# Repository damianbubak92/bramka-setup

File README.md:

# Bramka IoT - Setup & Development Repository

Repozytorium konfiguracji i kodu dla bramki IoT na AM62 SoC (SK-AM62B-P1 dev kit).

## Architektura

- **SoC**: TI AM62 (Cortex-A53 quad + Cortex-M4F + Cortex-R5F)
- **Linux**: Arago 2025.01 (kernel 6.18.13-ti, ARM64)
- **Komunikacja**: Linux ↔ M4F przez RPMsg (binary protocol z CRC16)
- **Język aplikacji Linux**: Go 1.23.x (instalowany przez `Gateway/Setup/modules/04-go.sh`)
- **Firmware M4F**: TI MCU+ SDK 12.00, NoRTOS

## Struktura repo

> Ten README opisuje **wczesny stan (sama bramka, RPMsg)**. Projekt urósł do
> **monorepo `SmartHome`** (engine M4F, CC1310 RF, nody, apka Android) — pełny
> aktualny stan, konwencje i Session Log w **`CLAUDE.md`**. (Repo na GitHub wciąż
> nazwany `bramka-setup`; może zostać przemianowany na `SmartHome`.)

```
SmartHome/                (zmigrowane z bramka-setup 2026-06-29)
├── Gateway/              # bramka (A53 Linux + M4F + CC1310 RF)
│   ├── Software/         #   Go: rpmsg-service (RPMsg bridge + HTTP/WS API, cgo)
│   ├── Firmware/         #   CCS: M4F (gateway_m4f) + CC1310 (gateway_cc1310)
│   ├── Setup/            #   setup.sh, modules/, systemd/, tools/, config.sh
│   └── Hardware/         #   carrier board (TODO)
├── Nodes/                # TempHumNode/{Firmware = temphum_node, Hardware}, Light/Solar (szkielety)
├── Apps/                 # MobileApp/AndroidApp/SmartHomeV2 (Android Studio); iOS/, WebApp/ (TODO)
├── Shared/               # Protocol/ (node_protocol.h, protocol.h, spi_frame.h — SINGLE SOURCE), KiCadLib/
└── Docs/
```

## Quick start

### 1. Instalacja bramki (od zera)
```bash
# 1. Świeży flash karty SD (Etcher)
# 2. SSH do bramki:
git clone https://github.com/damianbubak92/bramka-setup
cd bramka-setup/Gateway/Setup
sudo ./setup.sh    # network + tools + m4f firmware backup + GO INSTALL
reboot
# 3. Z laptopa:
Deploy-M4F                                            # custom M4F firmware
Deploy-Go -ServiceName rpmsg-service -Build           # build Go binary
Install-GoService -ServiceName rpmsg-service          # systemd unit
```

### 2. Workflow developerski

**M4F firmware** (z laptopa, PowerShell):
```powershell
# Build w CCS Theia (Ctrl+Shift+B)
Deploy-M4F                         # 5s logów
Deploy-M4F -LogForever             # logi do Ctrl+C
Deploy-M4F -NoLogs                 # bez logów
```
> `m4f-reload` (woła go `Deploy-M4F`) sam zatrzymuje `rpmsg-service` przed
> `echo stop` M4F i restartuje po starcie. Bez tego serwis wykryłby zniknięcie
> `/dev/rpmsg` jako PEER DEAD i zrobił reboot bramki w trakcie podmiany firmware.

**Go service** (z laptopa, PowerShell):
```powershell
Deploy-Go -ServiceName protocol-test -Build -Run
```

### 3. Monitor

```bash
ssh root@bramka-01
m4f-watch                          # live M4F trace
```

## Status (v5)

- ✅ Setup script (Linux configuration, network, tools, M4F firmware)
- ✅ M4F graceful shutdown handler (hot-swap firmware bez reboot)
- ✅ Go runtime (cgo działa, łączy się z shared C header)
- ✅ Binary protocol (CRC16-CCITT, packed wire format, big-endian)
- ✅ HELLO/HELLO_ACK exchange w binary protocol
- ✅ State machine: DISCONNECTED → HELLO_SENT → CONNECTED → DEAD
- ✅ Reliable DATA delivery (ACK + 3 retries z 1s timeout)
- ✅ Idempotency check (duplicate detection w M4F)
- ✅ EVENT (M4F→Linux autonomous events z ACK + retry)
- ✅ Bidirectional reliable messaging w pełni działa (~5ms RTT)
- ✅ **Warstwa A**: systemd watchdog dla Go service (`Restart=on-failure` + `StartLimitBurst=3`)
- ⏸️ **Warstwa B**: M4F self-watchdog (RTI) - skipped, do later
- ⏳ **Warstwa C**: M4F → Linux reset via DMSC
- ✅ **Warstwa D**: Linux HW watchdog (`/dev/watchdog` via systemd, `RuntimeWatchdogSec=30`) - konfigurowany przez `modules/05-watchdog.sh` (był zgubiony przy re-flashu, przywrócony 15.06.2026)
- ✅ **panic_on_oops=1** (`modules/06-kernel-panic.sh`): oops → pełny panic → łapie Warstwa D. Domyka lukę "oops kaleczy kernel ale systemd dalej klepie watchdog → nic nie łapie"
- ✅ **Boot accounting** (`modules/07-boot-accounting.sh`): licznik bootów + atrybucja przyczyny (breadcrumb Go / kernel panic / clean-shutdown / hard reset) + alarm reboot-storm (sparametryzowany `/etc/bramka/boot-accounting.conf`, default >3/24h). Persistent journald (50M). Podgląd: `bramka-reboots`
- ✅ **Non-root hardening** (`modules/08-hardening.sh`): `rpmsg-service` jako user `bramka` (zero capabilities). Device przez udev (grupa `bramka`), reboot przez path-unit (`bramka-reboot.path/.service`, bez roota/polkit). Binarka w `/opt/bramka` (Deploy-Go: cel `/opt/bramka`)
- ✅ **Heartbeat jednokierunkowy Linux→M4F**: Go pinguje M4F co 5s idle; brak odpowiedzi (~9s) = M4F martwy → **clean reboot** (`recoverByReboot`). M4F-initiated heartbeat usunięty (opcja A). Brak per-core reset M4F na AM62 - jedyna recovery to pełny reset SoC.
- ✅ **Cold-boot race fix**: serwis czeka na `/dev/rpmsg*` (`waitForM4FChrdev`) zamiast paść gdy M4F jeszcze się podnosi
- ⏳ Yocto build - later

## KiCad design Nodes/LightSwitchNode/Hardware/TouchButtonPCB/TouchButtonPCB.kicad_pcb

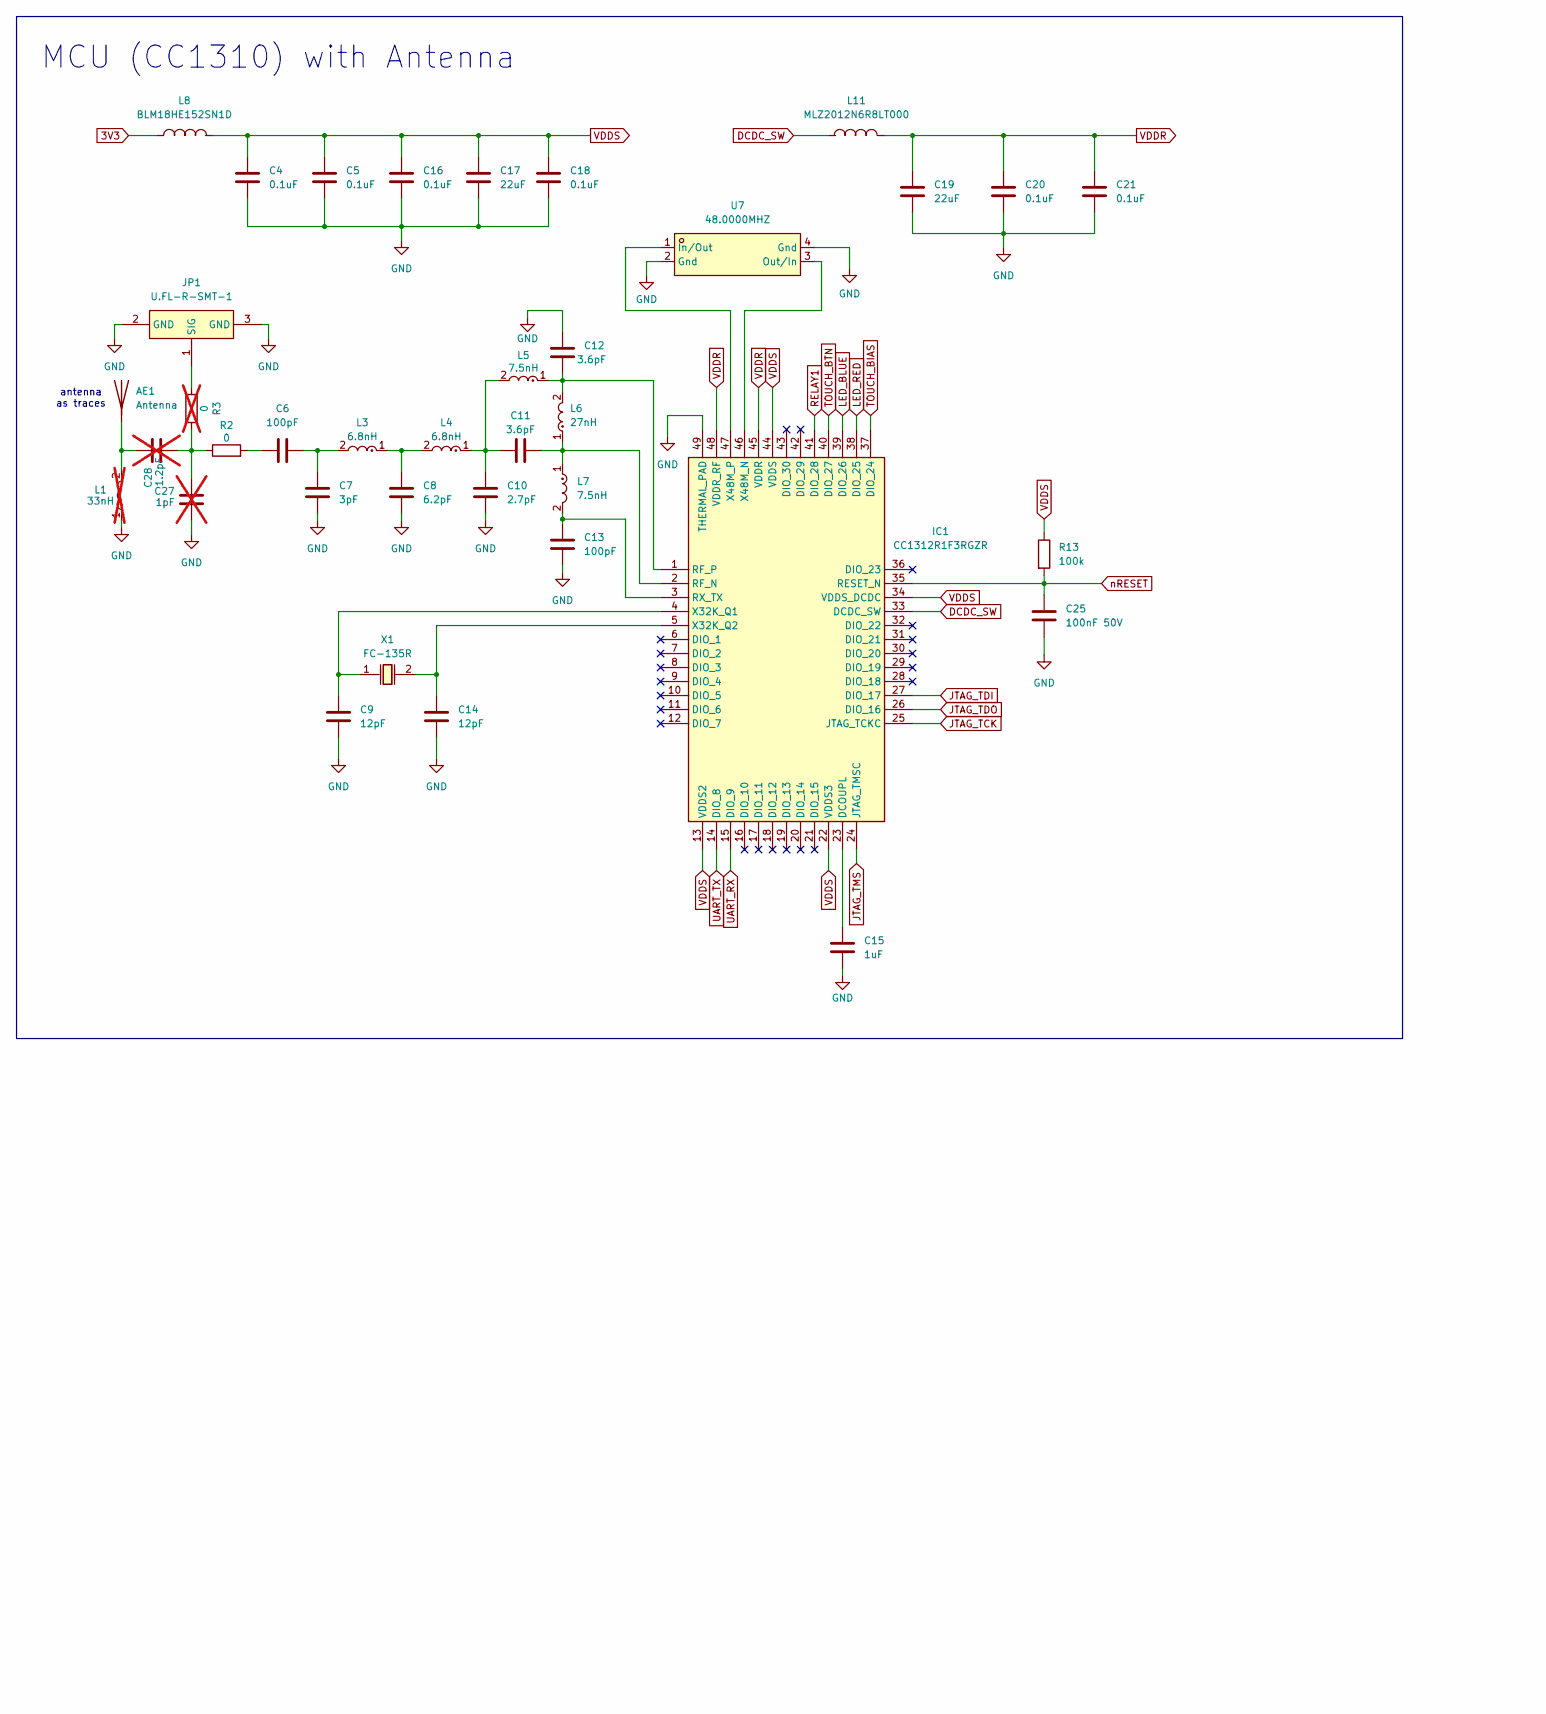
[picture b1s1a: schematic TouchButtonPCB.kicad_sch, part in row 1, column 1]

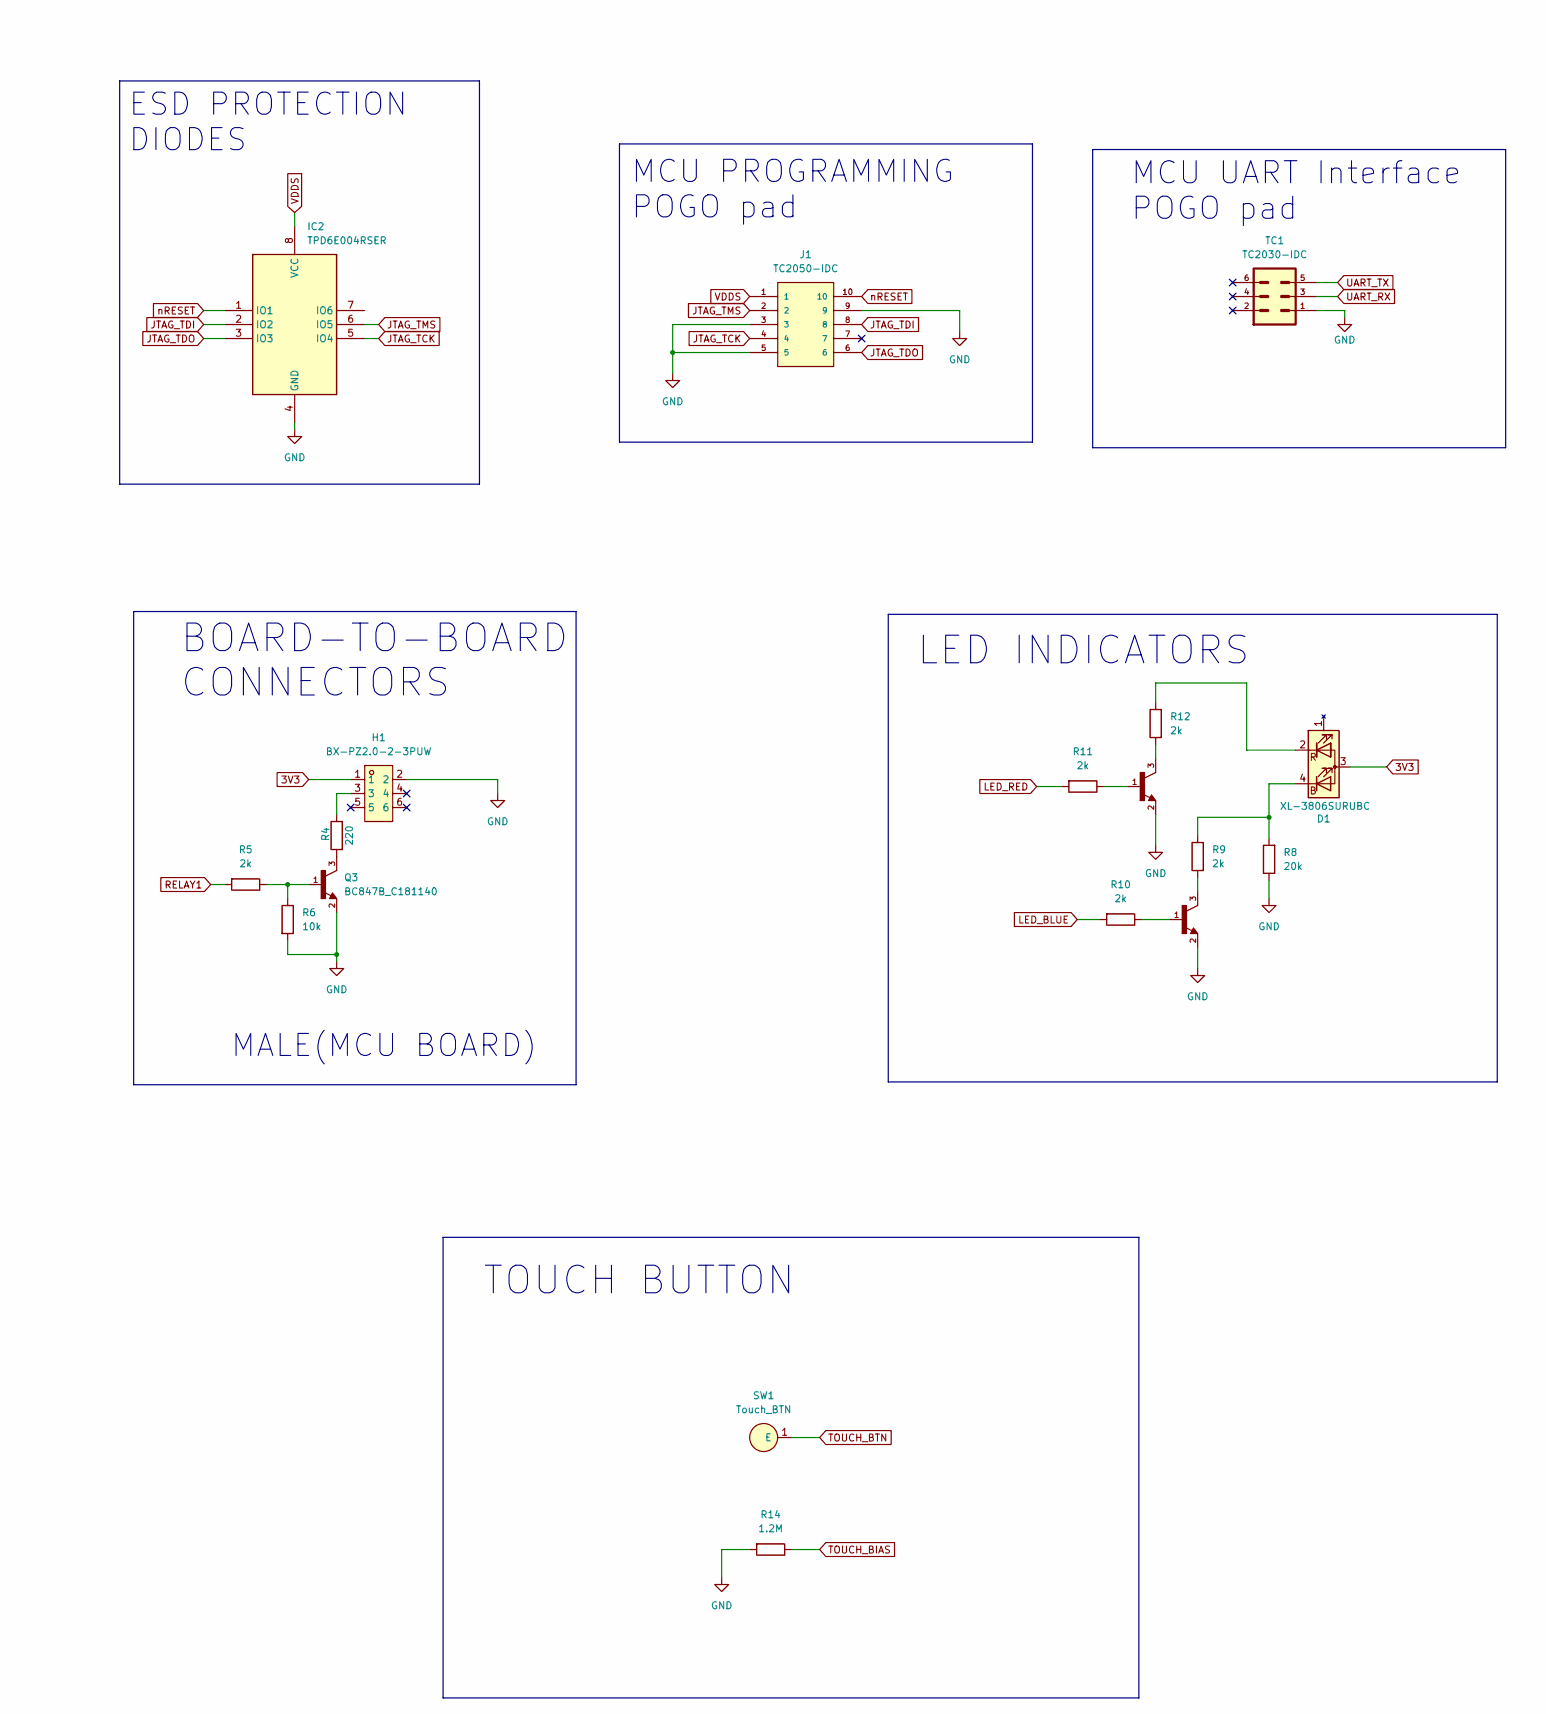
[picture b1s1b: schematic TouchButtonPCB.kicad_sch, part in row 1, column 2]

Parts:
AE1: Antenna; ANT_IFA_868M
C4, C5, C16, C18, C20, C21: 0.1uF; C_0402; MPN CC0402KRX7R7BB104; Mouser GRM155R70J104KA01D
C6, C13: 100pF; C_0402; MPN GRM1555C1H101JA01D; Mouser GRM1555C1H101JA01D
C7: 3pF; C_0402; MPN GJM1555C1H3R0BB01D; Mouser GRM1555C1H3R0CA01J
C8: 6.2pF; C_0402; MPN 0402CG6R2C500NT; Mouser GRM1555C1H6R2CA01J
C9: 12pF; C_0402; MPN GRM1555C1H120JA01D; Mouser GRM1555C1H120JA01D
C10: 2.7pF; C_0402; MPN GRM1555C1H2R7CA01D; Mouser GRM1555C1H2R7CA01D
C11, C12: 3.6pF; C_0402; MPN GRM1555C1H3R6CA01D; Mouser GRM1555C1H3R6CA01D
C14: 12pF; C_0402; MPN GRM1555C1H120JA01D; Mouser GRM1555C1H150JA01D
C15: 1uF; C_0402; MPN CL05A105KO5NNNC; Mouser GRM155R61C105KA12D
C17, C19: 22uF; C_0603; MPN CL05A226MQ5QUNC; Mouser GRM188R60J226MEA0D
C25: 100nF 50V; C_0402; MPN CC0402KRX7R9BB222; Mouser C0805C222K5RACTU
C27: 1pF; C_0402; MPN GJM1555C1H3R0BB01D; Mouser GRM1555C1H3R0CA01J; not fitted
C28: 1.2pF; C_0402; MPN GJM1555C1H3R0BB01D; Mouser GRM1555C1H3R0CA01J; not fitted
D1: XL-3806SURUBC; LED-SMD_4P-L3.8-W1.0_XL-3806RGBC-4L; MPN XL-3806SURUBC; JLC_Type Extended
H1: BX-PZ2.0-2-3PUW; HDR-SMD_6P-P2.00-V-M-R2-C3-LS6.5; MPN BX-PZ2.0-2-3PUW; LCSC Part C49326165
IC1: CC1312R1F3RGZR; CC1310_VQFN-48; Mouser Part Number 595-CC1310F128RGZR
IC2: TPD6E004RSER; Mouser Part Number 595-TPD6E004RSER
J1: TC2050-IDC; TAG-CONNECT_TC2050-IDC; PARTREV A
JP1: U.FL-R-SMT-1; RF-SMD_FRF05002-JSS103M; MPN U.FL-R-SMT-1(80); LCSC Part C88374
L1: 33nH; L_Polarized_0402; MPN LQG15HS8N2J02D; Mouser LQG15HS8N2J02D; not fitted
L3, L4: 6.8nH; L_Polarized_0402; MPN LQG15HS6N8J02D; Mouser LQG15HS6N8J02D
L5, L7: 7.5nH; L_Polarized_0402; MPN LQG15HS7N5J02D; Mouser LQG15HS7N5J02D
L6: 27nH; L_Polarized_0402; Mouser Part Number 81-LQG15HZ27NJ02D
L8: BLM18HE152SN1D; L0603; MPN BLM18HE152SN1D; LCSC Part C82155
L11: MLZ2012N6R8LT000; IND-SMD_L2.0-W1.3; MPN MLZ2012N6R8LT000; LCSC Part C82157
Q1, Q2, Q3: BC847B_C181140; SOT-23-3_L2.9-W1.3-P1.90-LS2.4-TL; MPN BC847B; LCSC Part C181140
R2: 0; R_0402; LCSC Part C106231
R3: 0; R_0402; LCSC Part C106231; not fitted
R4: 220; R_0805
R5, R10, R11: 2k; R_0402; MPN RC0402FR-072K2L; JLC_Type Extended
R6: 10k; R_0402; MPN RC0402FR-0710KL; JLC_Type Extended
R8: 20k; R_0402; MPN RC0402FR-0720KL; JLC_Type Extended
R9, R12: 2k; R_0402; MPN RC0402FR-072KL; JLC_Type Extended
R13: 100k; R_0402; MPN 0402WGF4752TCE; Mouser CRCW060347K5FKEA
R14: 1.2M; R_0402; MPN RC0402FR-072K2L; JLC_Type Extended
SW1: Touch_BTN; Touch_BTN_D12mm
TC1: TC2030-IDC
U7: 48.0000MHZ; CRYSTAL-SMD_4P-L3.2-W2.5-BL; MPN ABM8W-48.0000MHZ-7-D1X-T3; LCSC Part C6732653
X1: FC-135R; OSC-SMD_L3.2-W1.5; MPN X1A0001410003; LCSC Part C94276

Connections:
3V3: D1.3 (A), H1.1, L8.1
DCDC_SW: IC1.33 (DCDC_SW), L11.1
GND: C4.2, C5.2, C7.2, C8.2, C9.2, C10.2, C12.1, C13.2, C14.2, C15.2, C16.2, C17.2, C18.2, C19.2, C20.2, C21.2, C25.2, C27.2, H1.2, IC1.49 (THERMAL_PAD), IC2.4 (GND), J1.3, J1.5, J1.9, JP1.2 (GND), JP1.3 (GND), L1.1, Q1.2, Q2.2, Q3.2, R6.2, R8.1, R14.2, TC1.1, U7.2 (Gnd), U7.4 (Gnd)
JTAG_TCK: IC1.25 (JTAG_TCKC), IC2.5 (IO4), J1.4
JTAG_TDI: IC1.27 (DIO_17), IC2.2 (IO2), J1.8
JTAG_TDO: IC1.26 (DIO_16), IC2.3 (IO3), J1.6
JTAG_TMS: IC1.24 (JTAG_TMSC), IC2.6 (IO5), J1.2
LED_BLUE: IC1.39 (DIO_26), R10.2
LED_RED: IC1.38 (DIO_25), R11.2
unnamed: C6.1, C7.1, L3.2
unnamed: C6.2, R2.2
unnamed: C8.1, L3.1, L4.2
unnamed: C10.1, C11.1, L4.1, L5.2
unnamed: D1.4 (BK), R8.2, R9.2
unnamed: D1.2 (RK), R12.2
unnamed: H1.3, R4.2
unnamed: C15.1, IC1.23 (DCOUPL)
unnamed: C11.2, IC1.2 (RF_N), L6.1, L7.1
unnamed: C12.2, IC1.1 (RF_P), L5.1, L6.2
unnamed: C13.1, IC1.3 (RX_TX), L7.2
unnamed: C9.1, IC1.4 (X32K_Q1), X1.1 (OSC1)
unnamed: C14.1, IC1.5 (X32K_Q2), X1.2 (OSC2)
unnamed: IC1.46 (X48M_N), U7.3 (Out/In)
unnamed: IC1.47 (X48M_P), U7.1 (In/Out)
unnamed: JP1.1 (SIG), R3.1
unnamed: Q1.1, R11.1
unnamed: Q1.3, R12.1
unnamed: Q2.1, R10.1
unnamed: Q2.3, R9.1
unnamed: Q3.1, R5.1, R6.1
unnamed: Q3.3, R4.1
RELAY1: IC1.41 (DIO_28), R5.2
TOUCH_BIAS: IC1.37 (DIO_24), R14.1
TOUCH_BTN: IC1.40 (DIO_27), SW1.1 (E_1)
UART_RX: IC1.15 (DIO_9), TC1.3
UART_TX: IC1.14 (DIO_8), TC1.5
VDDR: C19.1, C20.1, C21.1, IC1.45 (VDDR), IC1.48 (VDDR_RF), L11.2
VDDS: C4.1, C5.1, C16.1, C17.1, C18.1, IC1.13 (VDDS2), IC1.22 (VDDS3), IC1.34 (VDDS_DCDC), IC1.44 (VDDS), IC2.8 (VCC), J1.1, L8.2, R13.1
nRESET: C25.1, IC1.35 (RESET_N), IC2.1 (IO1), J1.10, R13.2

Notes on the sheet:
MALE(MCU BOARD)
MCU (CC1310) with Antenna
TOUCH BUTTON
LED INDICATORS
BOARD-TO-BOARD CONNECTORS
antenna as traces
MCU PROGRAMMING POGO pad
ESD PROTECTION DIODES
MCU UART Interface POGO pad

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
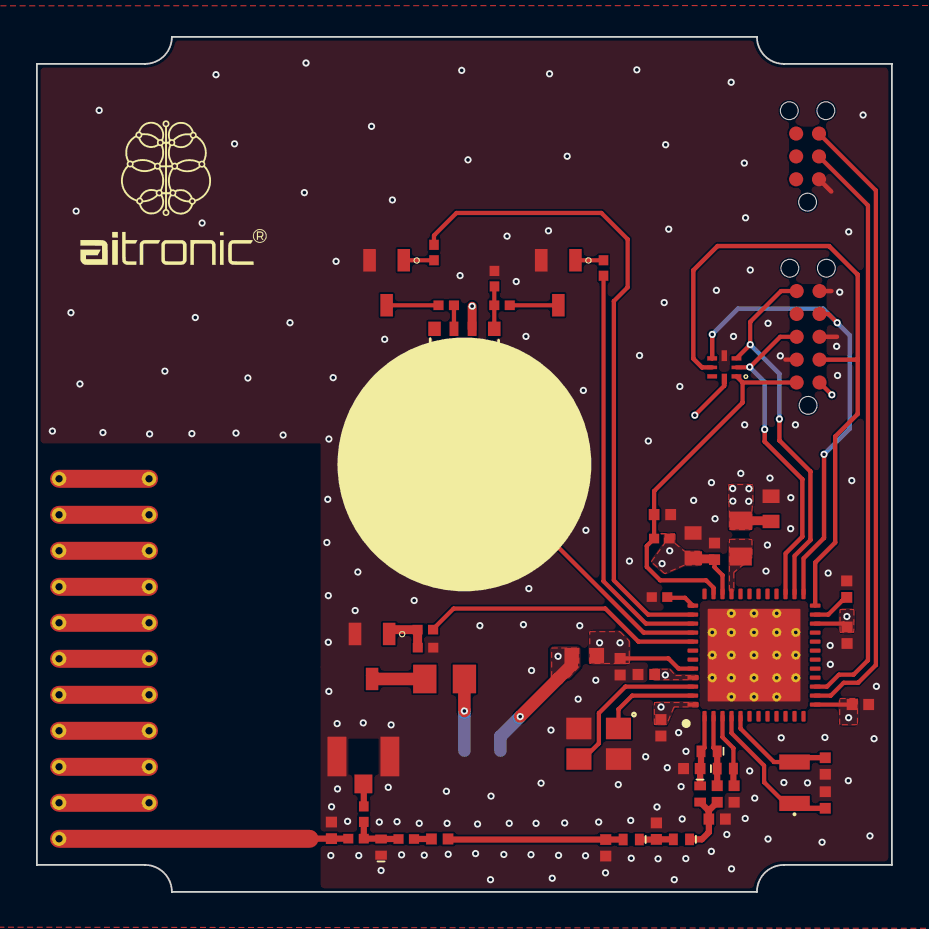
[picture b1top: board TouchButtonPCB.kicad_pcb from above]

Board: 4 copper layers, 47.5 x 47.5 mm, 55 parts (1 on the bottom side), 41 nets.

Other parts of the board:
R1: 0; R_0402

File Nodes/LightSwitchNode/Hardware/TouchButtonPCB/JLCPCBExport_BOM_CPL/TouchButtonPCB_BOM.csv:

Comment,Designator,Footprint,LCSC Part #
0.1uF,"C4,C5,C16,C18,C20,C21",SmartHome:C_0402,C60474
100pF,"C6,C13",SmartHome:C_0402,C77177
3pF,C7,SmartHome:C_0402,C88891
6.2pF,C8,SmartHome:C_0402,C41744
12pF,"C9,C14",SmartHome:C_0402,C76948
2.7pF,C10,SmartHome:C_0402,C76963
3.6pF,"C11,C12",SmartHome:C_0402,C913745
1uF,C15,SmartHome:C_0402,C29266
22uF,"C17,C19",SmartHome:C_0603,C86295
2.2nF 50V,C25,SmartHome:C_0402,C106861
XL-3806SURUBC,D1,SmartHome:LED-SMD_4P-L3.8-W1.0_XL-3806RGBC-4L,C5349972
BX-PZ2.0-2-3PUW,H1,SmartHome:HDR-SMD_6P-P2.00-V-M-R2-C3-LS6.5,C49326165
CC1312R1F3RGZR,IC1,SmartHome:CC1310_VQFN-48,C543014
TPD6E004RSER,IC2,SmartHome:TPD6E004RSER,C1973052
U.FL-R-SMT-1,JP1,SmartHome:RF-SMD_FRF05002-JSS103M,C88374
6.8nH,"L3,L4",SmartHome:L_Polarized_0402,C77110
7.5nH,"L5,L7",SmartHome:L_Polarized_0402,C98001
27nH,L6,SmartHome:L_Polarized_0402,C12669
BLM18HE152SN1D,L8,SmartHome:L0603,C82155
MLZ2012N6R8LT000,L11,SmartHome:IND-SMD_L2.0-W1.3,C82157
BC847B_C181140,"Q1,Q2,Q3",SmartHome:SOT-23-3_L2.9-W1.3-P1.90-LS2.4-TL,C181140
0,"R1,R2",SmartHome:R_0402,C106231
220,R4,SmartHome:R_0805,C843981
2k,R5,SmartHome:R_0402,C114762
10k,R6,SmartHome:R_0402,C60490
20k,R8,SmartHome:R_0402,C93942
2k,"R9,R10,R11,R12",SmartHome:R_0402,C60488
47.5k,R13,SmartHome:R_0402,C25896
1.2M,R14,SmartHome:R_0402,C60488
48.0000MHZ,U7,SmartHome:CRYSTAL-SMD_4P-L3.2-W2.5-BL,C6732653
FC-135R,X1,SmartHome:OSC-SMD_L3.2-W1.5,C94276

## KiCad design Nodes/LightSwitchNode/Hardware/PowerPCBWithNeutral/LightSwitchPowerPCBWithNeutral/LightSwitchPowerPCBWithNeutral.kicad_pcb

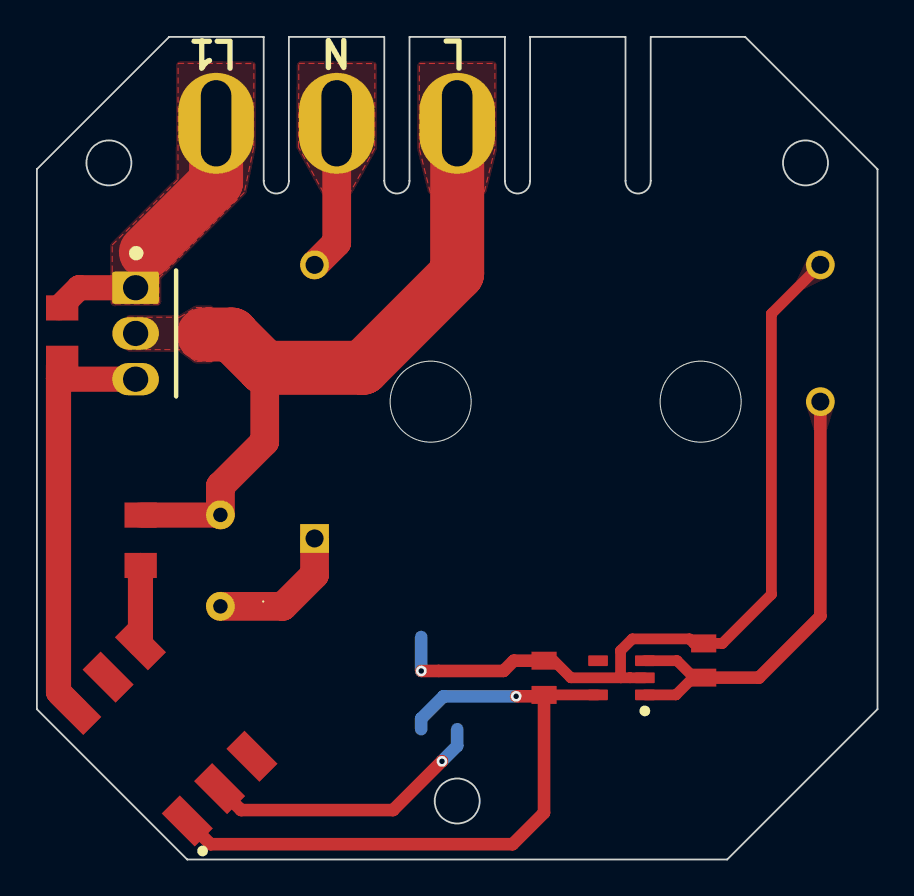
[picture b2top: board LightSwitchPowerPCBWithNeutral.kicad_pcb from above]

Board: 2 copper layers, 46.7 x 45.7 mm, 13 parts (1 on the bottom side), 10 nets.

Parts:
C1, C2: 1uF; C0805
J1, J5, J6: Brass_Screw_Terminal_Pad
Q3: BTA16-800BWRG; TO-220-3_L10.0-W4.5-P2.54-L
R2, R3: 330; R1206
R4: 47R 1W; R_Axial_DIN0309_L9.0mm_D3.2mm_P5.08mm_Vertical
U1: TPS7A2033PDBVR; SOT-23-5_L2.9-W1.6-P0.95-LS2.8-BR
U2: IRM-01-5; PWRM-TH_L33.7-W22.2_IRM-01-12
U3: BX-PM2.0-2-3PUW; HDR-SMD_6P-P2.00-V-F-R2-C3-S6.5
U4: MOC3063S-TA1; SMD-6_L7.3-W6.5-P2.54-LS10.2-BL

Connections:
3V3: C2.1, U1.5 (OUT), U3.1, U4.1
GND: C1.2, C2.2, U1.2 (GND), U2.13 (-V), U3.2
L: J6.1 (Pin_1_1), Q3.2, R2.2, R4.1
L1: J1.1 (Pin_1_1), Q3.1, R3.1
N: J5.1 (Pin_1_1), U2.24 (AC/N)
unnamed: Q3.3, R3.2, U4.6
unnamed: R2.1, U4.4
unnamed: C1.1, U1.1 (IN), U1.3 (EN), U2.12 (+V)
unnamed: R4.2, U2.1 (AC/L)
RELAY1: U3.3, U4.2

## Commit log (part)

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2026-06-11 Initial bramka setup automation
2026-06-12 v2: add shutdown handler docs, baseline firmware template, troubleshooting guide
2026-06-13 v3: Binary protocol with HELLO/HELLO_ACK working end-to-end
    - Added shared/protocol.h with CRC16-CCITT, packed wire format, big-endian
    - Added Go service in go-services/protocol-test/ using cgo for shared header
    - M4F firmware source archived in m4f-firmware/
    - Deploy-Go workflow in PowerShell (analog to Deploy-M4F)
    - docs/PROTOCOL.md describes the protocol design
    - docs/TROUBLESHOOTING.md updated with lessons from this iteration
2026-06-14 v4: Full bidirectional reliable messaging
    - Sequence number generator (auto-increment per direction)
    - Pending ACKs table (Go map, M4F static array)
    - Retry logic with 1s timeout + 3 retries + giveup
    - Idempotency check (duplicate detection in M4F)
    - EVENT (M4F-initiated messages with ACK + retry)
    - State machine: DISCONNECTED -> HELLO_SENT -> CONNECTED
2026-06-14 v5: Watchdog stack - layers A (systemd) and D (HW)
    - Warstwa A: systemd watchdog dla Go service (notify + WatchdogSec)
    - sd_notify minimalna implementacja w systemd_notify.go
    - watchdogKicker goroutine kickujący co WATCHDOG_USEC/2
    - debugDisableWatchdog dla test mode hang
    - Test A (kill -9): auto-restart w 2-3s
    - Test B (hang): SIGABRT + auto-restart w 12s
2026-06-15 Fix shell script permissions, add heartbeat patches, enforce LF line endings
2026-06-15 Make rpmsg-service unit safe: -test hello, on-failure restart, burst limit
2026-06-15 Add Go toolchain installation module (04-go.sh)
2026-06-15 Add CLAUDE.md - operating manual for Claude Code sessions
2026-06-15 Docs cleanup: reconcile watchdog/heartbeat/recovery state
    README + docs/WATCHDOG.md were stale: claimed Restart=always (it's
    on-failure), "smart heartbeat zrezygnowany" (it's one-way Linux->M4F
    and is the M4F-death detector), and Go 1.26.4 (it's 1.23.x).
    Update to reflect reality: Warstwa D configured via modules/05-watchdog.sh
    (was missing from setup, lost on re-flash), M4F death -> clean reboot
    (recoverByReboot; no per-core M4F reset on AM62, remoteproc stop wedges
